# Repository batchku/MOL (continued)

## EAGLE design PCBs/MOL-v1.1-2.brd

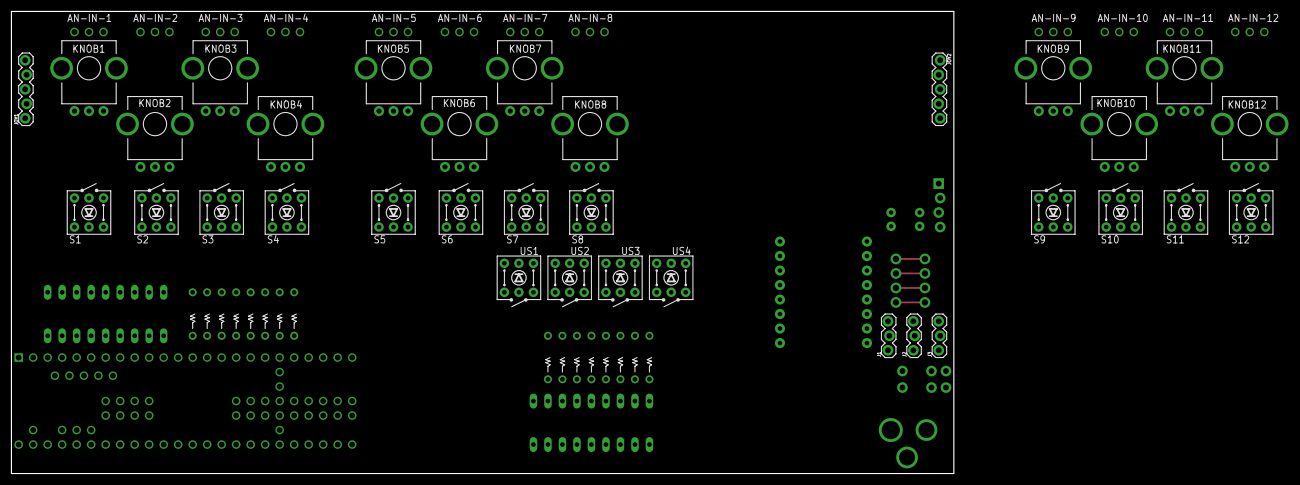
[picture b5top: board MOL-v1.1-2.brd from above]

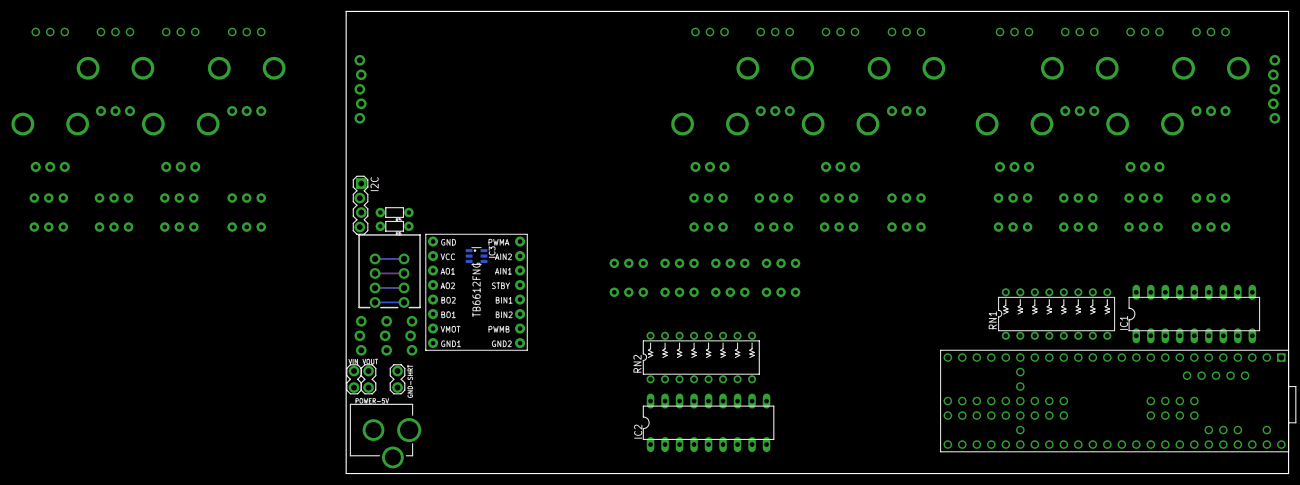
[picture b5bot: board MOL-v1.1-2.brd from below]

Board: 2 copper layers, 165.1 x 81.0 mm, 60 parts (15 on the bottom side), 80 nets, no tracks yet.

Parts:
AN-IN-1, AN-IN-2, AN-IN-3, AN-IN-4, AN-IN-5, AN-IN-6, AN-IN-7, AN-IN-8, AN-IN-9, AN-IN-10, AN-IN-11, AN-IN-12: 1X03_NO_SILK
GND-SHRT: 1X02_LOCK
I2C: 1X04_LOCK
IC1, IC2: ULN2803; DIL18
IC3: SN74LVC2G04DBV; SOT23-6
J1: SERVO 1; 1X03_LOCK@1
J2: SERVO 2; 1X03_LOCK@1
J3: SERVO 3; 1X03_LOCK@1
JOY1, JOY2: 1X05_LOCK
KNOB1, KNOB2, KNOB3, KNOB4, KNOB5, KNOB6, KNOB7, KNOB8, KNOB9, KNOB10, KNOB11, KNOB12: TRIM-PCB-9MM
MOTORS1: SPRINGTERMINAL-2.54MM-4
POWER-5V: DCJACK_2MM_PTH
R5, R6: 1/6W-RES
RN1, RN2: 330; RESISTOR-NET-8P-DIL16
S1, S2, S3, S4, S5, S6, S7, S8, S9, S10, S11, S12: SW-LEDPTH; TR2-SWITCH-MOMENTARY-LED
TEENSY: TEENSY3_6--ALLPINS; T36
U$7: POLOLU_TB6612FNG
US1, US2, US3, US4: SW-LEDPTH; TR2-SWITCH-MOMENTARY-LED
VIN: 1X02_LOCK
VOUT: 1X02_LOCK

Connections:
+3V3: AN-IN-1.1, AN-IN-2.1, AN-IN-3.1, AN-IN-4.1, AN-IN-5.1, AN-IN-6.1, AN-IN-7.1, AN-IN-8.1, AN-IN-9.1, AN-IN-10.1, AN-IN-11.1, AN-IN-12.1, I2C.1, IC3.5, JOY1.2, JOY2.2, KNOB1.1, KNOB2.1, KNOB3.1, KNOB4.1, KNOB5.1, KNOB6.1, KNOB7.1, KNOB8.1, KNOB9.1, KNOB10.1, KNOB11.1, KNOB12.1, R5.1, R6.1, TEENSY.3V3(1), TEENSY.3V3(2), TEENSY.3V3(3), TEENSY.3V3(4), U$7.STBY, U$7.VCC
+5V: IC1.10, IC2.10, J1.2, J2.2, J3.2, POWER-5V.PWR, VIN.1
AGND: AN-IN-1.3, AN-IN-2.3, AN-IN-3.3, AN-IN-4.3, AN-IN-5.3, AN-IN-6.3, AN-IN-7.3, AN-IN-8.3, AN-IN-9.3, AN-IN-10.3, AN-IN-11.3, AN-IN-12.3, JOY1.1, JOY2.1, KNOB1.3, KNOB2.3, KNOB3.3, KNOB4.3, KNOB5.3, KNOB6.3, KNOB7.3, KNOB8.3, KNOB9.3, KNOB10.3, KNOB11.3, KNOB12.3, TEENSY.AGND
AN1: AN-IN-1.2, AN-IN-5.2, AN-IN-9.2, KNOB1.2, KNOB5.2, KNOB9.2, TEENSY.14
AN2: AN-IN-2.2, AN-IN-6.2, AN-IN-10.2, KNOB2.2, KNOB6.2, KNOB10.2, TEENSY.15
AN3: AN-IN-3.2, AN-IN-7.2, AN-IN-11.2, KNOB3.2, KNOB7.2, KNOB11.2, TEENSY.16
AN4: AN-IN-4.2, AN-IN-8.2, AN-IN-12.2, KNOB4.2, KNOB8.2, KNOB12.2, TEENSY.33
B1: S1.1, S5.1, S9.1, TEENSY.11
B2: S2.1, S6.1, S10.1, TEENSY.12
B3: S3.1, S7.1, S11.1, TEENSY.24
B4: S4.1, S8.1, S12.1, TEENSY.25
GND: GND-SHRT.2, I2C.2, IC1.9, IC2.9, IC3.2, J1.1, J2.1, J3.1, S1.3, S2.3, S3.3, S4.3, S5.3, S6.3, S7.3, S8.3, S9.3, S10.3, S11.3, S12.3, TEENSY.G0, TEENSY.G1, TEENSY.G2, TEENSY.G3, TEENSY.G4, TEENSY.G5, TEENSY.G6, U$7.GND, US1.3, US2.3, US3.3, US4.3, VIN.2, VOUT.2
GND_MOT: GND-SHRT.1, POWER-5V.GND, U$7.GND1, U$7.GND2
I2C_SCL: I2C.3, R5.2
I2C_SDA: I2C.4, R6.2
JOYB1: JOY1.5, TEENSY.1
JOYB2: JOY2.5, TEENSY.0
JOYH1: JOY1.3, TEENSY.20
JOYH2: JOY2.3, TEENSY.18
JOYV1: JOY1.4, TEENSY.19
JOYV2: JOY2.4, TEENSY.17
L1: IC1.8, TEENSY.2
L2: IC1.7, TEENSY.3
L3: IC1.6, TEENSY.4
L4: IC1.5, TEENSY.5
L5: IC1.4, TEENSY.6
L6: IC1.3, TEENSY.7
L7: IC1.2, TEENSY.8
L8: IC1.1, TEENSY.23
L9: IC2.8, TEENSY.29
L10: IC2.7, TEENSY.30
L11: IC2.6, TEENSY.31
L12: IC2.5, TEENSY.32
LED1: RN1.H2, S1.C, S5.C, S9.C
LED2: RN1.G2, S2.C, S6.C, S10.C
LED3: RN1.F2, S3.C, S7.C, S11.C
LED4: RN1.E2, S4.C, S8.C, S12.C
M_AIN: IC3.3, TEENSY.40, U$7.AIN1
M_BIN: IC3.1, TEENSY.41, U$7.BIN2
M_PWMA: TEENSY.21, U$7.PWMA
M_PWMB: TEENSY.22, U$7.PWMB
unnamed: IC3.6, U$7.BIN1
unnamed: IC3.4, U$7.AIN2
unnamed: IC1.18, RN1.A1
unnamed: IC1.17, RN1.B1
unnamed: IC1.16, RN1.C1
unnamed: IC1.15, RN1.D1
unnamed: IC1.14, RN1.E1
unnamed: IC1.13, RN1.F1
unnamed: IC1.12, RN1.G1
unnamed: IC1.11, RN1.H1
unnamed: IC2.18, RN2.A1
unnamed: IC2.17, RN2.B1
unnamed: IC2.16, RN2.C1
unnamed: IC2.15, RN2.D1
unnamed: IC2.14, RN2.E1
unnamed: IC2.12, RN2.G1
unnamed: IC2.11, RN2.H1
unnamed: IC2.13, RN2.F1
unnamed: MOTORS1.P$1, U$7.BO1
unnamed: MOTORS1.P$2, U$7.BO2
unnamed: MOTORS1.P$3, U$7.AO2
unnamed: MOTORS1.P$4, U$7.AO1
S1: J1.3, TEENSY.9
S2: J2.3, TEENSY.10
S3: J3.3, TEENSY.49
UB1: TEENSY.57, US1.1
UB2: TEENSY.56, US2.1
UB3: TEENSY.55, US3.1
UB4: TEENSY.54, US4.1
UL1: IC2.4, TEENSY.53
UL2: IC2.3, TEENSY.52
UL3: IC2.2, TEENSY.51
UL4: IC2.1, TEENSY.50
ULED1: RN2.D2, US1.C
ULED2: RN2.C2, US2.C
ULED3: RN2.B2, US3.C
ULED4: RN2.A2, US4.C
V+: S1.A, S2.A, S3.A, S4.A, S5.A, S6.A, S7.A, S8.A, S9.A, S10.A, S11.A, S12.A, US1.A, US2.A, US3.A, US4.A
VMOT: U$7.VMOT, VOUT.1

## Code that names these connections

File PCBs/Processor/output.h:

//------------------------------------------------------
//Thiis file is automatically generated with pinlister.py
//------------------------------------------------------

int M_JOYB	= 0;
int S_JOYB	= 1;
int L1	= 2;
int L2	= 3;
int L3	= 4;
int L4	= 5;
int L5	= 6;
int L6	= 7;
int L7	= 8;
int S1	= 9;
int S2	= 10;
int B1	= 11;
int B2	= 12;
int AN1	= 14;
int AN2	= 15;
int AN3	= 16;
int M_JOYV	= 17;
int M_JOYH	= 18;
int S_JOYV	= 19;
int S_JOYH	= 20;
int M_PWMA	= 21;
int M_PWMB	= 22;
int L8	= 23;
int B3	= 24;
int B4	= 25;
int B5	= 26;
int B6	= 27;
int B7	= 28;
int L9	= 29;
int L10	= 37;
int L11	= 50;
int L12	= 49;
int AN4	= 33;
int AN5	= 34;
int AN6	= 35;
int AN7	= 36;
int AN8	= 39;
int M_AIN	= 40;
int M_BIN	= 41;
int B8	= 42;
int B9	= 43;
int B10	= 44;
int B11	= 45;
int B12	= 46;
int I2C_SCL	= 47;
int I2C_SDA	= 48;
int U1	= 51;
int U2	= 52;
int U3	= 53;
int U4	= 54;
int AN11	= A10;
int AN12	= A11;
int AN9	= A21;
int AN10	= A22;

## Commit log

2017-07-11 arduino code added
2017-07-11 arduino mk4
2017-07-12 MOL.h added
2017-07-12 netlist
2017-07-12 file reorganization for arduino world
2017-07-13 pinlist processor to generate arduino header
2017-07-13 signal name changes in MOL PCB v1.1
2017-07-13 arduino code
2017-07-14 Processor working, refactored Arduino code
2017-07-14 clean up
2017-07-15 version v2-2 of MOL board, teensy breakout board for modularized setup
2017-07-15 version v2-1 of MOL board, ACTUATOR and STRIP modules
2017-07-15 MOL PCB v2-1 and Modules revisions
2017-07-17 MOL updates
2017-07-17 Arduino update
2017-07-17 rerouted board
2017-07-17 reroute + Arduino stuff
2017-07-17 updates to teensy breakout
2017-07-18 pd folder
2017-07-18 pd stuff
2017-07-19 Changed LED CC#s so they match with note output numbers from the buttons
2017-07-19 Pd update
2017-07-24 mol.gui
2017-07-25 pd cahnges
2017-07-25 test fix
2017-07-25 new mol.strip patch with copy in the name
2017-07-25 less outlets
2017-07-26 mol library
2017-07-26 renamed objects and cleaned up test.pd
2017-07-26 MIDI user numbers change
